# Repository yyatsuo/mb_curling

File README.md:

# About The Project
mb_curling is a small project to build a curling robot using BBC micro:bit.
I started this project for an event organized by volunteers of students and graduates at a cyber university. 

# Getting Started
Please visit [mb_curling wiki on github](https://github.com/yyatsuo/mb_curling/wiki) for BOM, build instructions, and a programming guide.

# Contribution
If you have a suggestion that would make this better, please fork the repo and create a pull request.
You can also simply open an issue with the tag "enhancement". 
Thanks😊

# License
Distributed under the Solderpad Hardware License V2.1. See ```LICENSE.txt``` for more information.

# Acknowledgement
Without these great open-source software, I wouldn't be able to start my project.
Thanks to all the developers who contributed to these projects!
* [FreeCAD](https://www.freecad.org/)
* [KiCad](https://www.kicad.org/)

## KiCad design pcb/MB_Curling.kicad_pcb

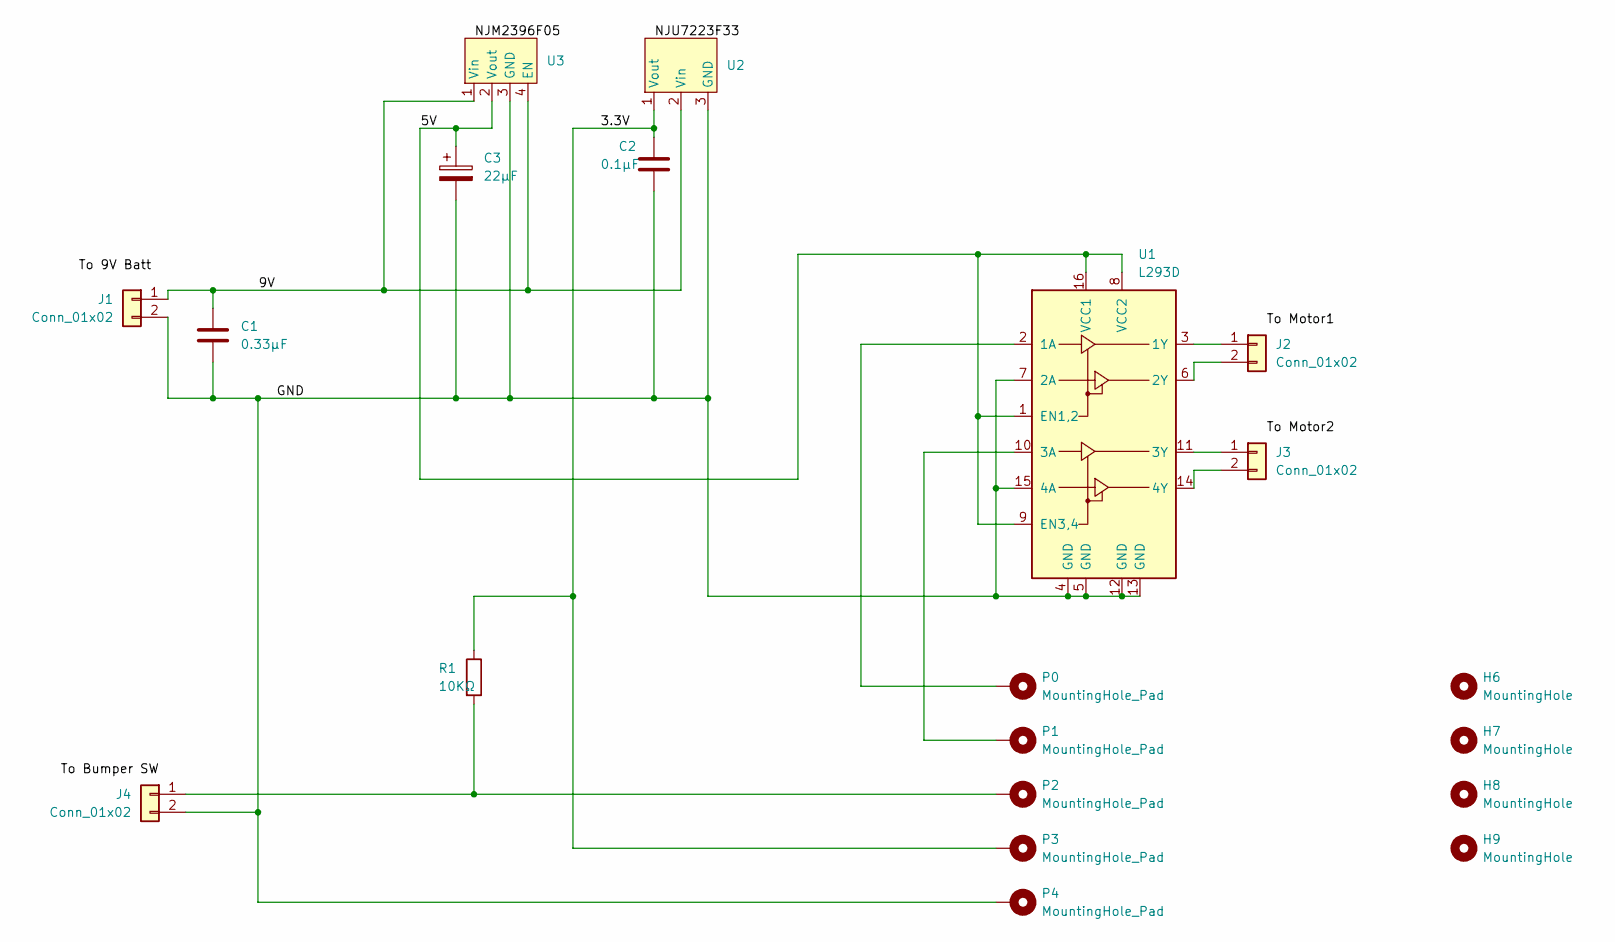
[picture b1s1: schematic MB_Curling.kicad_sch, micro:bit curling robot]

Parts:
C1: 0.33μF; C_Disc_D3.0mm_W1.6mm_P2.50mm
C2: 0.1μF; C_Disc_D3.0mm_W1.6mm_P2.50mm
C3: 22μF; CP_Radial_D5.0mm_P2.50mm
H6, H7, H8, H9: MountingHole; MountingHole_3.2mm_M3
J1, J2, J3, J4: Conn_01x02; PinHeader_1x02_P2.54mm_Vertical
P0, P1, P2, P3, P4: MountingHole_Pad; MountingHole_3.2mm_M3_DIN965_Pad
R1: 10KΩ; R_Axial_DIN0207_L6.3mm_D2.5mm_P10.16mm_Horizontal
U1: L293D; DIP-16_W7.62mm
U2: TO-220-3_Horizontal_TabDown
U3: TO-220-4_Horizontal_TabDown

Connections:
/3.3V: C2.1, P3.1, R1.1, U2.1 (Vout)
/5V: C3.1, U1.1 (EN1,2), U1.8 (VCC2), U1.9 (EN3,4), U1.16 (VCC1), U3.2 (Vout)
/9V: C1.1, J1.1, U2.2 (Vin), U3.1 (Vin), U3.4 (EN)
/GND: C1.2, C2.2, C3.2, J1.2, J4.2, P4.1, U1.4 (GND), U1.5 (GND), U1.7 (2A), U1.12 (GND), U1.13 (GND), U1.15 (4A), U2.3 (GND), U3.3 (GND)
unnamed: J2.1, U1.3 (1Y)
unnamed: J2.2, U1.6 (2Y)
unnamed: J3.1, U1.11 (3Y)
unnamed: J3.2, U1.14 (4Y)
unnamed: J4.1, P2.1, R1.2
unnamed: P0.1, U1.2 (1A)
unnamed: P1.1, U1.10 (3A)

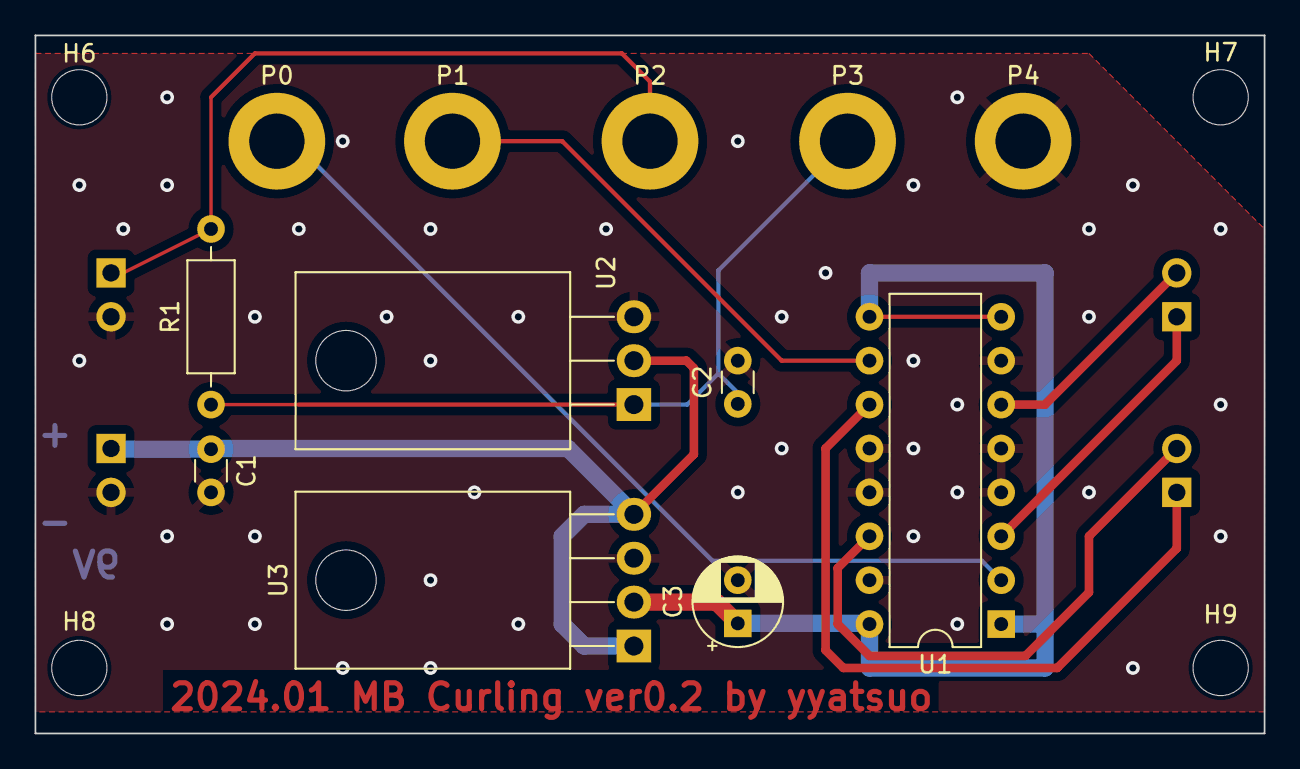
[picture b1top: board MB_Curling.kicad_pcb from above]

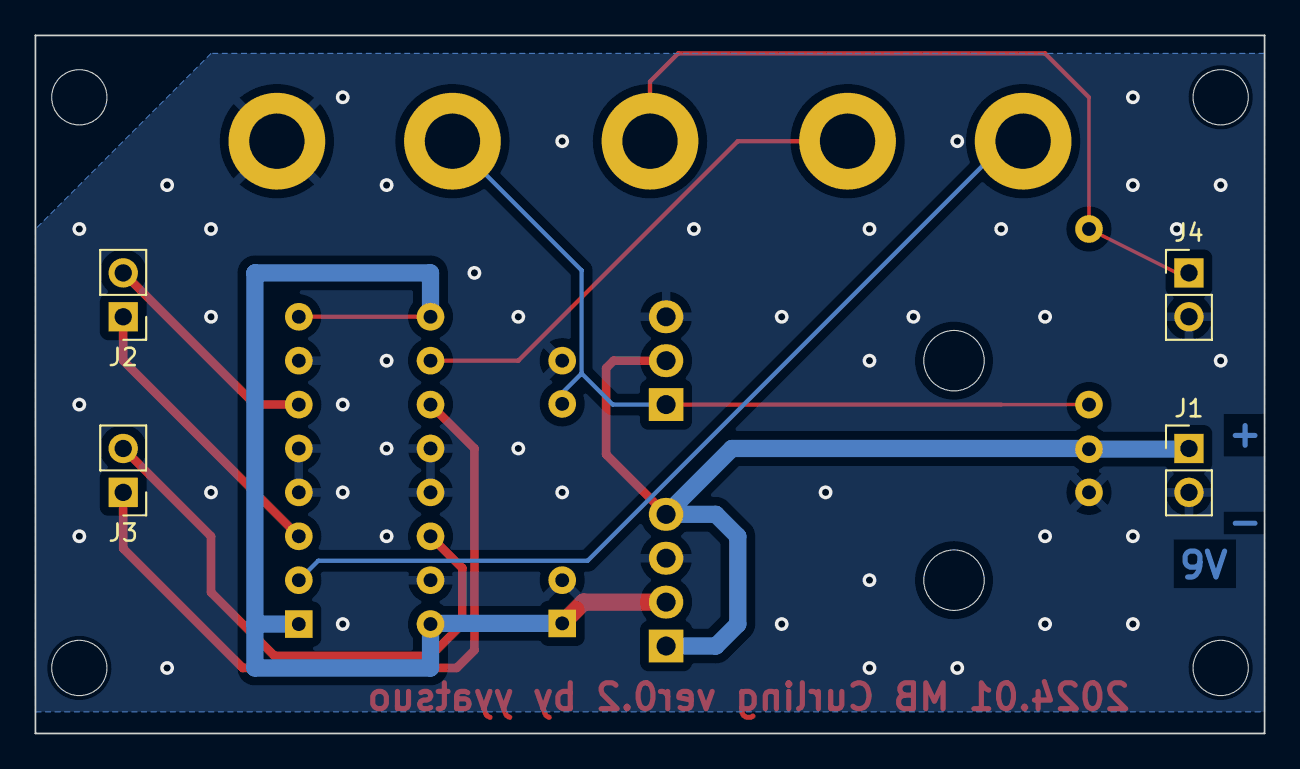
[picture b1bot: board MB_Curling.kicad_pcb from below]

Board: 2 copper layers, 71.1 x 40.4 mm, 20 parts (4 on the bottom side), 11 nets.

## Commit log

2024-01-27 Update license information
